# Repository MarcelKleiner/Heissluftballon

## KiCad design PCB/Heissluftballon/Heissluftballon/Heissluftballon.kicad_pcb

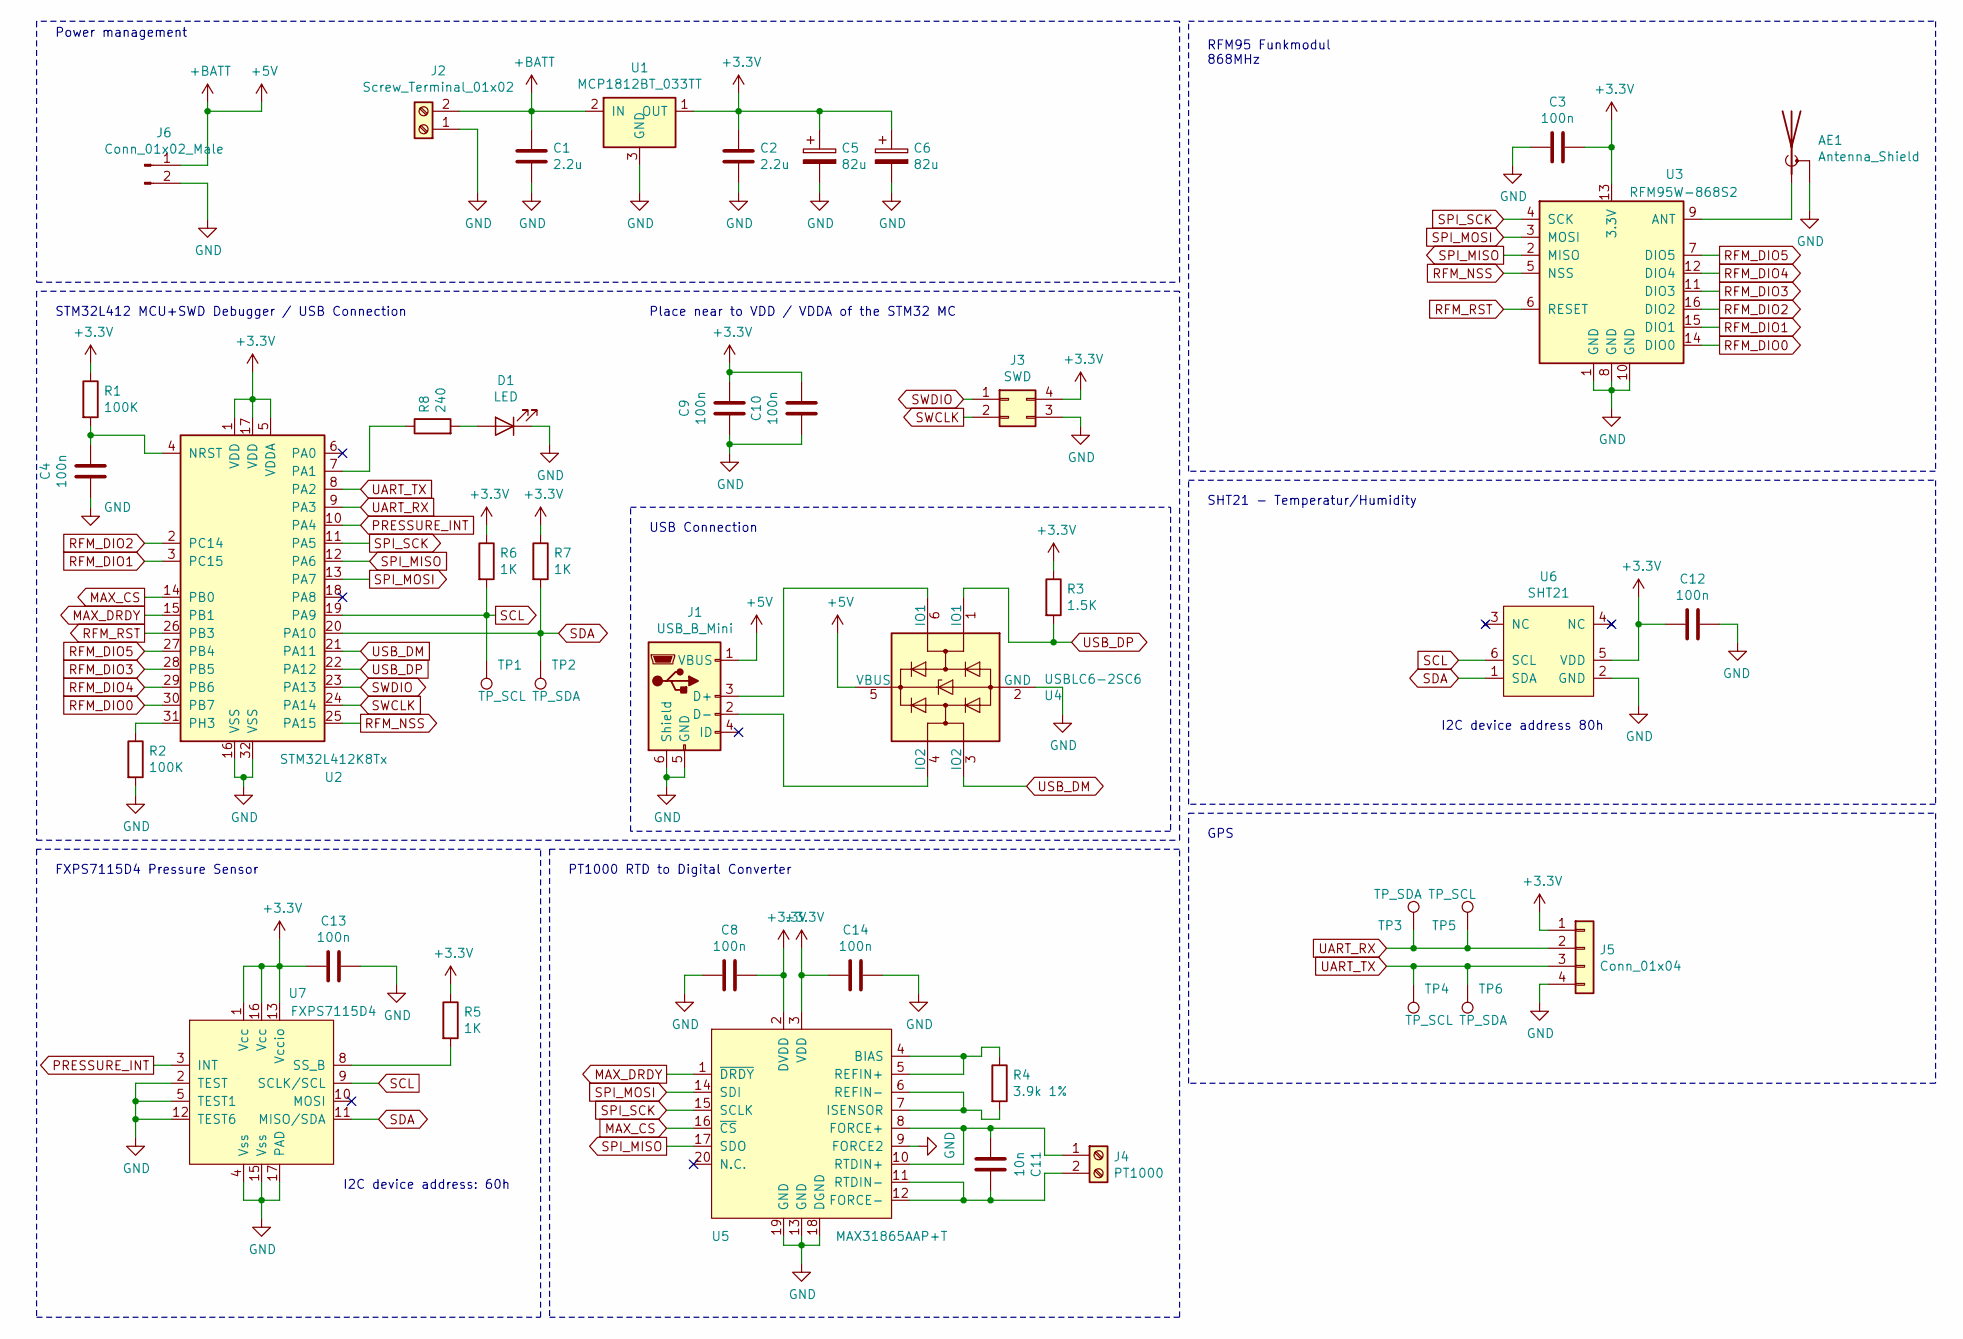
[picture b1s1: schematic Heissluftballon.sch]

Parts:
AE1: Antenna_Shield; SMA_Amphenol_901-144_Vertical
C1, C2: 2.2u; C_0603_1608Metric
C3, C4, C8, C9, C10, C12, C13, C14: 100n; C_0603_1608Metric
C5, C6: 82u; CP_Elec_6.3x5.9
C11: 10n; C_0603_1608Metric
D1: LED; LED_0603_1608Metric
J1: USB_B_Mini; USB_Mini-B_Lumberg_2486_01_Horizontal
J2: Screw_Terminal_01x02; TerminalBlock_Phoenix_MPT-0,5-2-2.54_1x02_P2.54mm_Horizontal
J3: SWD; PinHeader_2x02_P2.54mm_Vertical
J4: PT1000; TerminalBlock_Phoenix_MPT-0,5-2-2.54_1x02_P2.54mm_Horizontal
J5: Conn_01x04; PinSocket_1x04_P2.54mm_Vertical
J6: Conn_01x02_Male; PinHeader_1x02_P2.54mm_Vertical
R1, R2: 100K; R_0603_1608Metric
R3: 1.5K; R_0603_1608Metric
R4: 3.9k 1%; R_0603_1608Metric
R5, R6, R7: 1K; R_0603_1608Metric
R8: 240; R_0603_1608Metric
TP1, TP4, TP5: TP_SCL; TestPoint_Pad_D1.0mm
TP2, TP3, TP6: TP_SDA; TestPoint_Pad_D1.0mm
U1: MCP1812BT_033TT; SOT-23
U2: STM32L412K8Tx; LQFP-32_7x7mm_P0.8mm
U3: RFM95W-868S2; HOPERF_RFM9XW_SMD
U4: USBLC6-2SC6; SOT-23-6
U5: MAX31865AAP+T; SSOP-20_5.3x7.2mm_P0.65mm
U6: SHT21; DFN-6-1EP_3x3mm_P1mm_EP1.5x2.4mm
U7: FXPS7115D4; HQFN-16-1EP_4x4mm_P0.8mm_EP2.7x2.7mm

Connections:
+3V3: C2.1, C3.2, C5.1, C6.1, C8.2, C9.2, C10.2, C12.2, C13.1, C14.1, J3.4, J5.1, R1.1, R3.1, R5.1, R6.1, R7.1, U1.1 (OUT), U2.1 (VDD), U2.5 (VDDA), U2.17 (VDD), U3.13 (3.3V), U5.2 (DVDD), U5.3 (VDD), U6.5 (VDD), U7.1 (Vcc), U7.13 (Vccio), U7.16 (Vcc)
+5V: C1.1, J1.1 (VBUS), J2.2, J6.1, U1.2 (IN), U4.5 (VBUS)
GND: AE1.2 (Shield), C1.2, C2.2, C3.1, C4.1, C5.2, C6.2, C8.1, C9.1, C10.1, C12.1, C13.2, C14.2, D1.1 (K), J1.5 (GND), J1.6 (Shield), J2.1, J3.3, J5.4, J6.2, R2.2, U1.3 (GND), U2.16 (VSS), U2.32 (VSS), U3.1 (GND), U3.8 (GND), U3.10 (GND), U4.2 (GND), U5.9 (FORCE2), U5.13 (GND), U5.18 (DGND), U5.19 (GND), U6.2 (GND), U7.2 (TEST), U7.4 (Vss), U7.5 (TEST1), U7.12 (TEST6), U7.15 (Vss), U7.17 (PAD)
MAX_CS: U2.14 (PB0), U5.16 (~CS)
MAX_DRDY: U2.15 (PB1), U5.1 (~DRDY)
unnamed: AE1.1 (A), U3.9 (ANT)
unnamed: C4.2, R1.2, U2.4 (NRST)
unnamed: C11.1, J4.1, U5.8 (FORCE+), U5.10 (RTDIN+)
unnamed: C11.2, J4.2, U5.11 (RTDIN-), U5.12 (FORCE-)
unnamed: D1.2 (A), R8.2
unnamed: J1.2 (D-), U4.4 (IO2)
unnamed: J1.3 (D+), U4.6 (IO1)
unnamed: R2.1, U2.31 (PH3)
unnamed: R4.1, U5.4 (BIAS), U5.5 (REFIN+)
unnamed: R4.2, U5.6 (REFIN-), U5.7 (ISENSOR)
unnamed: R5.2, U7.8 (SS_B)
unnamed: R8.1, U2.7 (PA1)
PRESSURE_INT: U2.10 (PA4), U7.3 (INT)
RFM_DIO0: U2.30 (PB7), U3.14 (DIO0)
RFM_DIO1: U2.3 (PC15), U3.15 (DIO1)
RFM_DIO2: U2.2 (PC14), U3.16 (DIO2)
RFM_DIO3: U2.28 (PB5), U3.11 (DIO3)
RFM_DIO4: U2.29 (PB6), U3.12 (DIO4)
RFM_DIO5: U2.27 (PB4), U3.7 (DIO5)
RFM_NSS: U2.25 (PA15), U3.5 (NSS)
RFM_RST: U2.26 (PB3), U3.6 (RESET)
SCL: R6.2, TP1.1, U2.19 (PA9), U6.6 (SCL), U7.9 (SCLK/SCL)
SDA: R7.2, TP2.1, U2.20 (PA10), U6.1 (SDA), U7.11 (MISO/SDA)
SPI_MISO: U2.12 (PA6), U3.2 (MISO), U5.17 (SDO)
SPI_MOSI: U2.13 (PA7), U3.3 (MOSI), U5.14 (SDI)
SPI_SCK: U2.11 (PA5), U3.4 (SCK), U5.15 (SCLK)
SWCLK: J3.2, U2.24 (PA14)
SWDIO: J3.1, U2.23 (PA13)
UART_RX: J5.2, TP3.1, TP5.1, U2.9 (PA3)
UART_TX: J5.3, TP4.1, TP6.1, U2.8 (PA2)
USB_DM: U2.21 (PA11), U4.3 (IO2)
USB_DP: R3.2, U2.22 (PA12), U4.1 (IO1)

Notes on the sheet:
Place near to VDD / VDDA of the STM32 MC
GPS
SHT21 - Temperatur/Humidity
RFM95 Funkmodul 868MHz
Power management
STM32L412 MCU+SWD Debugger / USB Connection
USB Connection
PT1000 RTD to Digital Converter
FXPS7115D4 Pressure Sensor
I2C device address: 60h
I2C device address 80h

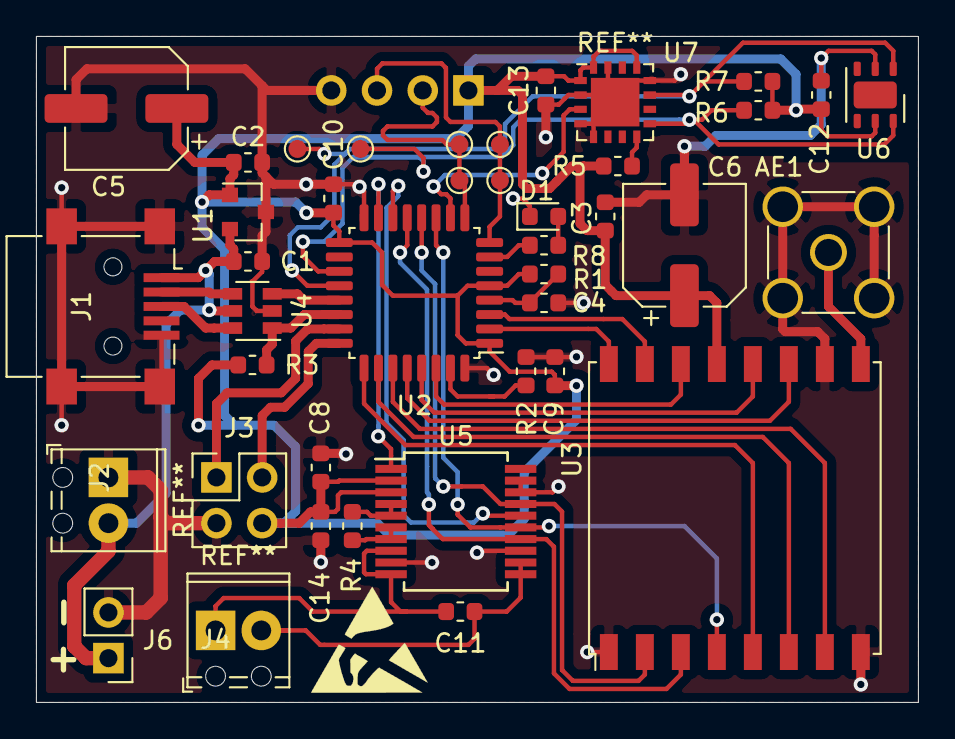
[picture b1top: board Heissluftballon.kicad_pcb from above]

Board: 2 copper layers, 49.0 x 37.0 mm, 42 parts (1 on the bottom side), 37 nets.

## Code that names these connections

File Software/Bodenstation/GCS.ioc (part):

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Mcu.Name=STM32L412K8Tx
Mcu.Package=LQFP32
Mcu.UserName=STM32L412K8Tx
PA0-CK_IN.GPIOParameters=GPIO_Label
PA0-CK_IN.GPIO_Label=NC
PA0-CK_IN.Signal=GPIO_Analog
PA1.GPIOParameters=GPIO_Label
PA1.GPIO_Label=LED
PA1.Signal=GPIO_Output
PA10.Mode=I2C
PA10.Signal=I2C1_SDA
PA11.Mode=Device
PA11.Signal=USB_DM
PA12.Mode=Device
PA12.Signal=USB_DP
PA13\ (JTMS/SWDIO).Mode=Serial_Wire
PA13\ (JTMS/SWDIO).Signal=SYS_JTMS-SWDIO
PA14\ (JTCK/SWCLK).Mode=Serial_Wire
PA14\ (JTCK/SWCLK).Signal=SYS_JTCK-SWCLK
PA15\ (JTDI).GPIOParameters=GPIO_Label
PA15\ (JTDI).GPIO_Label=RFM_NSS
PA15\ (JTDI).Signal=GPIO_Output
PA2.Mode=Asynchronous
PA2.Signal=USART2_TX
PA3.Mode=Asynchronous
PA3.Signal=USART2_RX
PA4.GPIOParameters=GPIO_Label
PA4.GPIO_Label=PRESSURE_INT
PA4.Signal=GPXTI4
PA5.Mode=Full_Duplex_Master
PA5.Signal=SPI1_SCK
PA6.Mode=Full_Duplex_Master
PA6.Signal=SPI1_MISO
PA7.Mode=Full_Duplex_Master
PA7.Signal=SPI1_MOSI
PA8.GPIOParameters=GPIO_Label
PA8.GPIO_Label=NC
PA8.Signal=GPIO_Analog
PA9.Mode=I2C
PA9.Signal=I2C1_SCL
PB0.GPIOParameters=GPIO_Label
PB0.GPIO_Label=MAX_CS
PB0.Signal=GPIO_Output
PB1.GPIOParameters=GPIO_Label
PB1.GPIO_Label=MAX_DRDY
PB1.Signal=GPIO_Output
PB3\ (JTDO/TRACESWO).GPIOParameters=GPIO_Label
PB3\ (JTDO/TRACESWO).GPIO_Label=RFM_RST
PB3\ (JTDO/TRACESWO).Signal=GPIO_Output
PB4\ (NJTRST).GPIOParameters=GPIO_Label
PB4\ (NJTRST).GPIO_Label=RFM_DIO5
PB4\ (NJTRST).Signal=GPIO_Input
PB5.GPIOParameters=GPIO_Label
PB5.GPIO_Label=RFM_DIO3
PB5.Signal=GPIO_Input
PB6.GPIOParameters=GPIO_Label
PB6.GPIO_Label=RFM_DIO4
PB6.Signal=GPIO_Input
PB7.GPIOParameters=GPIO_Label
PB7.GPIO_Label=RFM_DIO0
PB7.Signal=GPIO_Input
PC14-OSC32_IN\ (PC14).GPIOParameters=GPIO_Label
PC14-OSC32_IN\ (PC14).GPIO_Label=RFM_DIO2
PC14-OSC32_IN\ (PC14).Signal=GPIO_Input
PC15-OSC32_OUT\ (PC15).GPIOParameters=GPIO_Label
PC15-OSC32_OUT\ (PC15).GPIO_Label=RFM_DIO1
PC15-OSC32_OUT\ (PC15).Signal=GPIO_Input
RCC.HSE_VALUE=8000000
RCC.SYSCLKFreq_VALUE=32000000
RCC.SYSCLKSource=RCC_SYSCLKSOURCE_PLLCLK
board=custom

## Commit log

2020-04-11 initial comit using Gmap nuget using LiveCharts
2020-04-14 update GUI / mc software
2020-04-17 update software
2020-04-20 update software RM95
2020-04-21 update RFM95
2020-04-23 update Software mc/GUI - RFM working with lora protocol
2020-04-24 update GUI
2020-04-29 update GUI / add seperator string MC
